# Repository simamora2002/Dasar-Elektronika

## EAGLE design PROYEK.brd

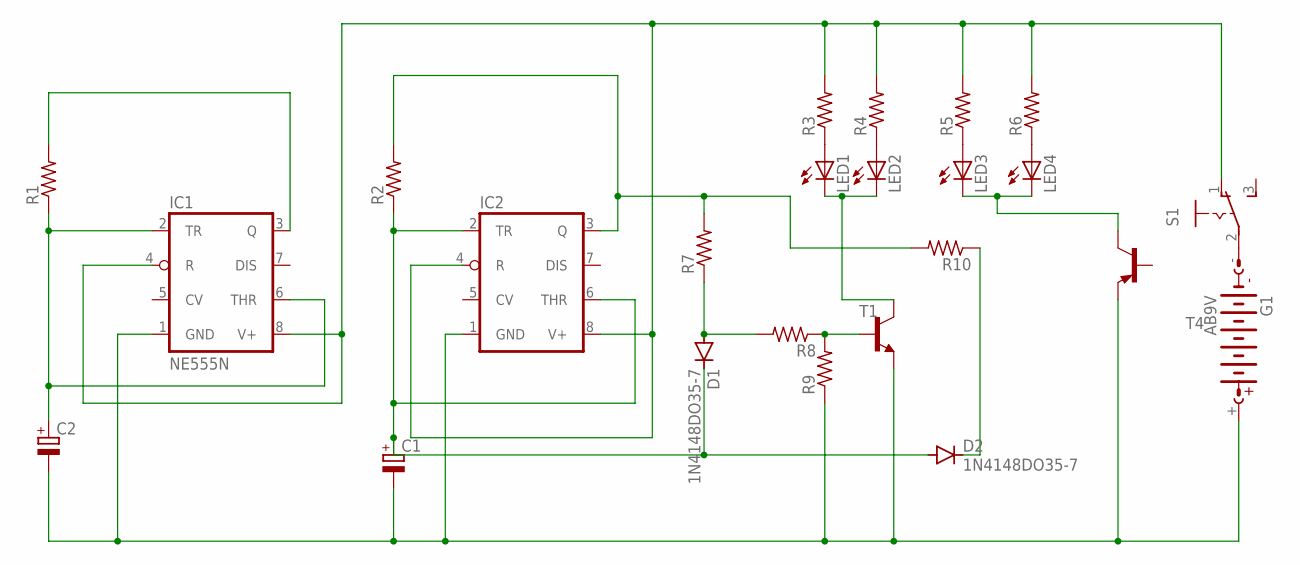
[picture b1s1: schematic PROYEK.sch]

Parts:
C1: CPOL-EUE3.5-8; E3,5-8
C2: CPOL-EUE3.5-10; E3,5-10
D1, D2: 1N4148DO35-7; DO35-7
G1: AB9V
IC1, IC2: NE555N; DIL08
LED1, LED2, LED3, LED4: LED5MM
R1, R2: R-US_0204/2V; 0204V
R3, R4, R5, R6, R7, R8, R9, R10: R-US_0204/7; 0204/7
S1: 255SB
T1: BC547-NPN-TO92-CBE; TO92-CBE
T4: BC557C-PNP-TO92-EBC; TO92-EBC

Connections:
unnamed: LED1.A, R3.1
unnamed: LED2.A, R4.1
unnamed: LED3.A, R5.1
unnamed: LED4.A, R6.1
unnamed: G1.-, S1.2
unnamed: IC2.3 (Q), R2.2, R7.2, R10.2
unnamed: C1.-, C2.-, G1.+, IC1.1 (GND), IC2.1 (GND), R9.1, T1.E, T4.E
unnamed: C2.+, IC1.2 (TR), IC1.6 (THR), R1.1
unnamed: IC1.4 (R), IC1.8 (V+), IC2.4 (R), IC2.8 (V+), R3.2, R4.2, R5.2, R6.2, S1.1 (O)
unnamed: IC1.3 (Q), R1.2
unnamed: C1.+, D1.C, D2.A, IC2.2 (TR), IC2.6 (THR), R2.1
unnamed: D1.A, R7.1, R8.2
unnamed: R8.1, R9.2, T1.B
unnamed: LED1.K (C), LED2.K (C), T1.C
unnamed: LED3.K (C), LED4.K (C), T4.C
unnamed: D2.C, R10.1

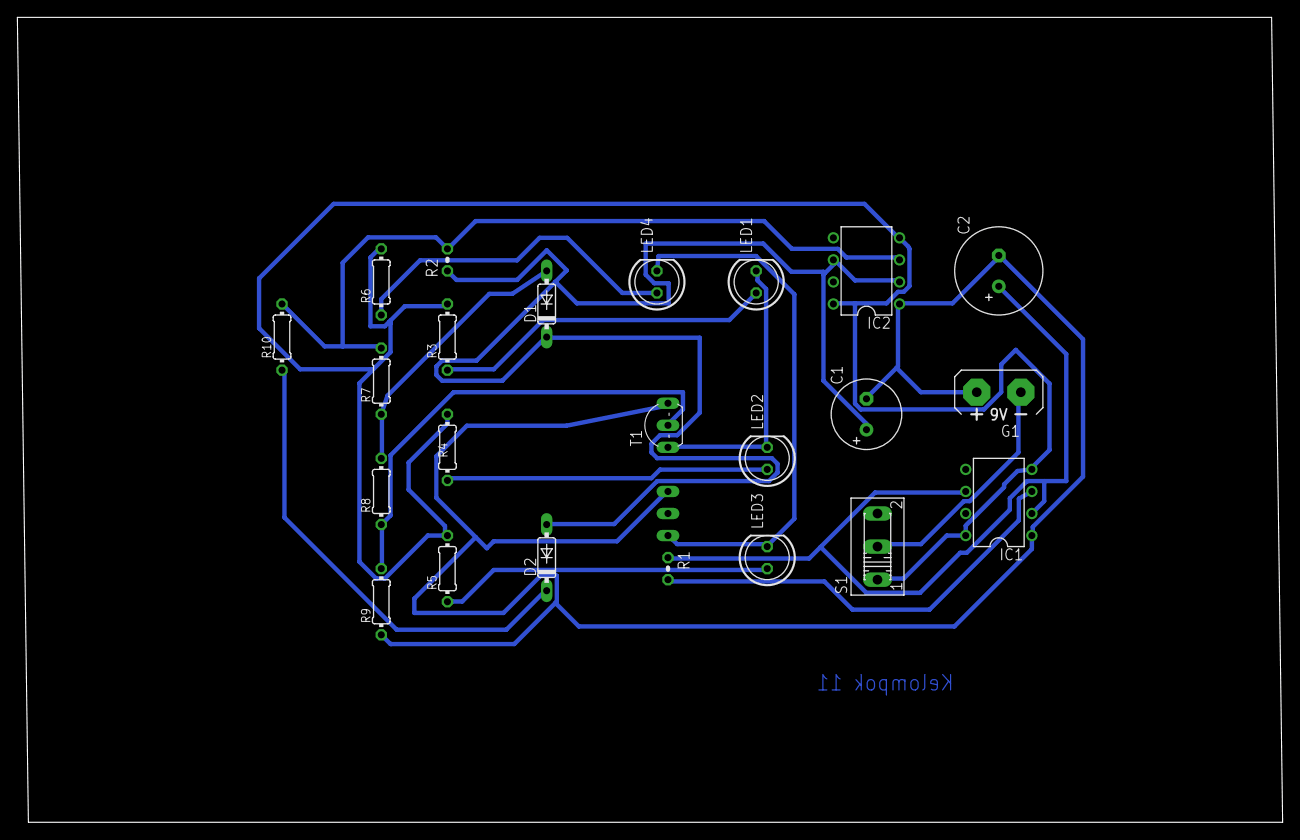
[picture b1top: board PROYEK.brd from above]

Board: 2 copper layers, 145.7 x 92.7 mm, 24 parts (1 on the bottom side), 16 nets.
